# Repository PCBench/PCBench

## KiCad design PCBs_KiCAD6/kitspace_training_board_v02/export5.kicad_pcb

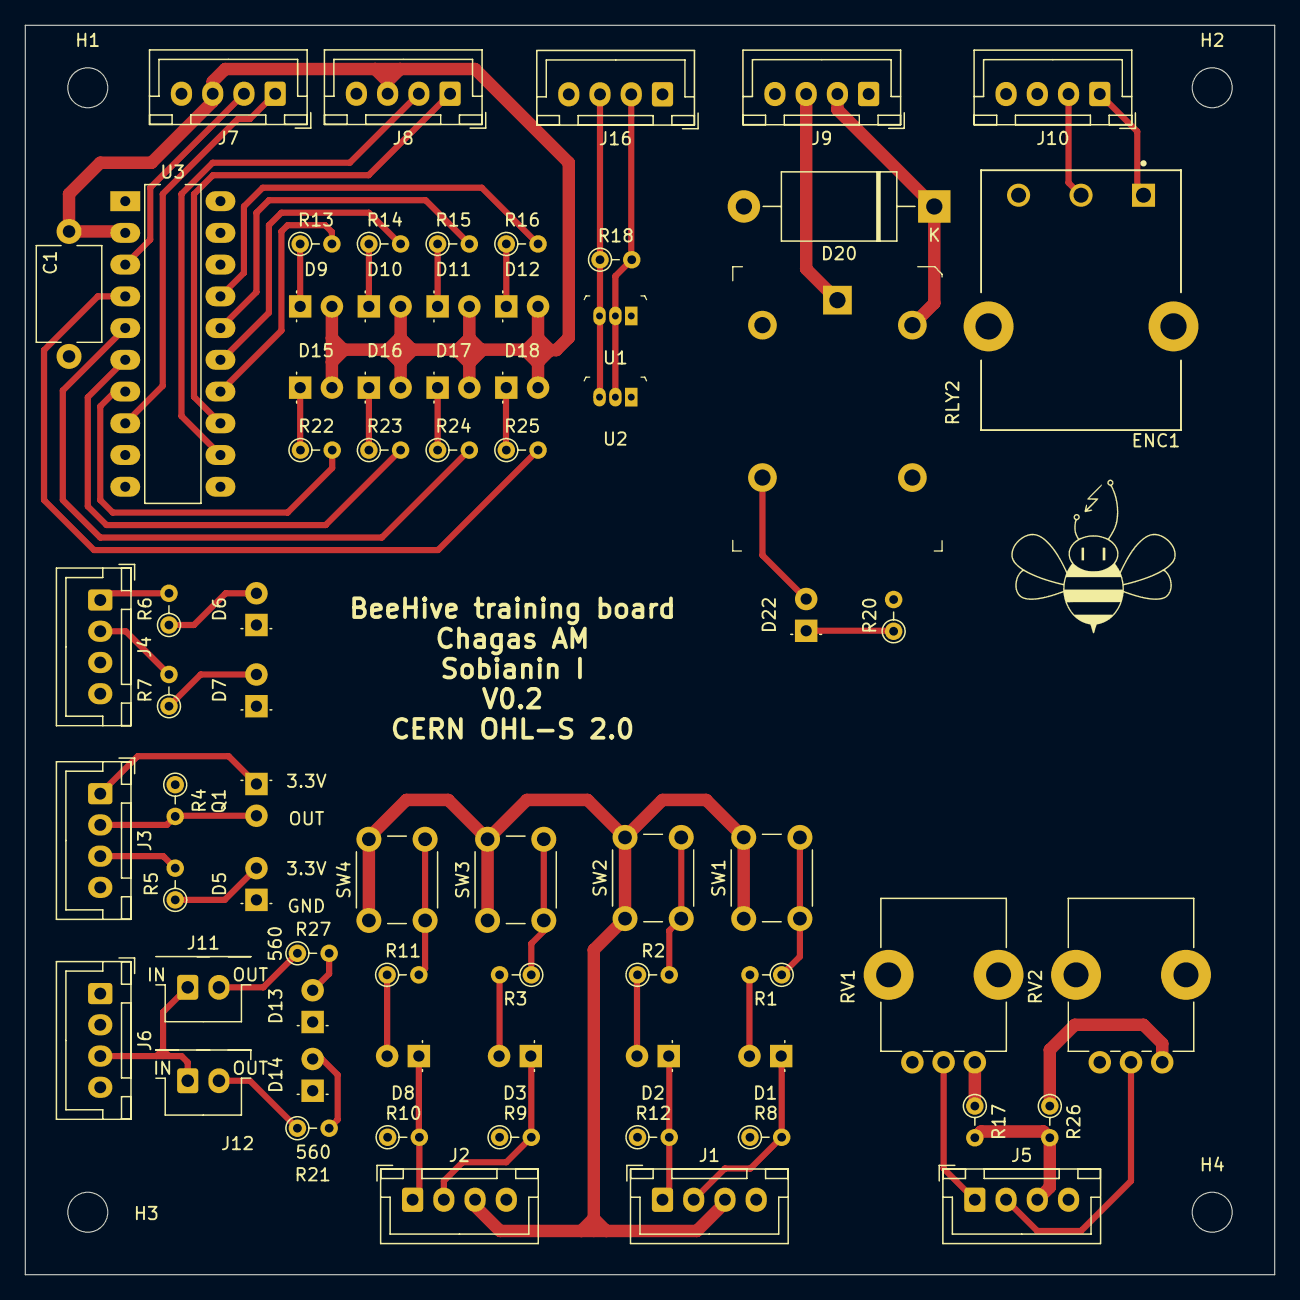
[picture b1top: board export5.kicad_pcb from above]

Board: 2 copper layers, 100.0 x 100.0 mm, 75 parts (0 on the bottom side), 61 nets.

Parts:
C1: 100nf; C_Disc_D7.5mm_W5.0mm_P10.00mm
D1, D2, D3, D6, D7, D8, D9, D10, D11, D12, D13, D14, D15, D16, D17, D18, D22: LED; LED_D3.0mm
D5: IR LED; LED_D3.0mm
D20: D_Schottky; D_DO-201AE_P15.24mm_Horizontal
ENC1: PEC16-4015F-N0024; Bourns_Inc.-PEC16-4015F-N0024-MFG
H1, H2, H3, H4: MountingHole; MountingHole_3.2mm_M3_DIN965
J1, J2, J3, J4, J5, J6, J7, J8, J9, J10, J16: Conn_01x04; JST_XH_B4B-XH-A_1x04_P2.50mm_Vertical
J11, J12: Conn_01x02; JST_XH_B2B-XH-A_1x02_P2.50mm_Vertical
Q1: Q_Photo_NPN; LED_D3.0mm
R1, R2, R3, R6, R7, R11: 220; R_Axial_DIN0204_L3.6mm_D1.6mm_P2.54mm_Vertical
R4: 10k; R_Axial_DIN0204_L3.6mm_D1.6mm_P2.54mm_Vertical
R5: 47; R_Axial_DIN0204_L3.6mm_D1.6mm_P2.54mm_Vertical
R8, R9, R10, R12: 1k; R_Axial_DIN0204_L3.6mm_D1.6mm_P2.54mm_Vertical
R13, R14, R15, R16, R20, R21, R22, R23, R24, R25, R27: 560; R_Axial_DIN0204_L3.6mm_D1.6mm_P2.54mm_Vertical
R17, R26: 5.6k; R_Axial_DIN0204_L3.6mm_D1.6mm_P2.54mm_Vertical
R18: 4.7k; R_Axial_DIN0204_L3.6mm_D1.6mm_P2.54mm_Vertical
RLY2: G5LE-14_DC5; Relay_THT_G5LE-14
RV1, RV2: 1k; Potentiometer_Alps_RK09K_Single_Vertical
SW1, SW2, SW3, SW4: SW_Push; SW_PUSH_6mm
U1, U2: DS18S20_; TO-92-3
U3: TPIC6595; DIP-20_W7.62mm_LongPads

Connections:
GND: C1.1, D5.1, D6.1, D7.1, D13.1, D14.1, D20.2, ENC1.C, J1.4, J2.4, J3.4, J4.4, J5.4, J6.4, J7.4, J8.4, J9.4, J10.4, J16.4, R4.1, R8.1, R9.1, R10.1, R12.1, R20.2, RLY2.2, RV1.3, RV2.3, U1.1, U2.1, U3.1, U3.9, U3.10, U3.11, U3.19, U3.20
unnamed: D1.1, J1.2, R8.2
unnamed: D1.2, R1.2
unnamed: D2.1, J1.1, R12.2
unnamed: D2.2, R2.1
unnamed: D3.1, J2.2, R9.2
unnamed: D3.2, R3.2
unnamed: D5.2, R5.1
unnamed: D6.2, R6.1
unnamed: D7.2, R7.1
unnamed: D8.1, J2.1, R10.2
unnamed: D8.2, R11.1
unnamed: D9.1, R13.1
unnamed: D10.1, R14.1
unnamed: D11.1, R15.1
unnamed: D12.1, R16.1
unnamed: D13.2, R27.2
unnamed: D14.2, R21.2
unnamed: D15.1, R22.1
unnamed: D16.1, R23.1
unnamed: D17.1, R24.1
unnamed: D18.1, R25.1
unnamed: D20.1, J9.2, RLY2.5
unnamed: D22.1, R20.1
unnamed: D22.2, RLY2.3
unnamed: ENC1.A, J10.1
unnamed: ENC1.B, J10.2
unnamed: J3.1, Q1.1
unnamed: J3.2, Q1.2, R4.2
unnamed: J3.3, R5.2
unnamed: J4.1, R6.2
unnamed: J4.2, R7.2
unnamed: J5.1, RV1.2
unnamed: J5.2, RV2.2
unnamed: J5.3, R17.2, R26.2
unnamed: J6.3, J11.1, J12.1
unnamed: J7.1, U3.8
unnamed: J7.2, U3.3
unnamed: J8.1, U3.13
unnamed: J8.2, U3.12
unnamed: J9.3, RLY2.1
unnamed: J16.2, R18.2, U1.2, U2.2
unnamed: R1.1, SW1.2
unnamed: R2.2, SW2.2
unnamed: R3.1, SW3.2
unnamed: R11.2, SW4.2
unnamed: R13.2, U3.14
unnamed: R14.2, U3.15
unnamed: R15.2, U3.16
unnamed: R16.2, U3.17
unnamed: R17.1, RV1.1
unnamed: J12.2, R21.1
unnamed: R22.2, U3.7
unnamed: R23.2, U3.6
unnamed: R24.2, U3.5
unnamed: R25.2, U3.4
unnamed: R26.1, RV2.1
unnamed: J11.2, R27.1
button_5v: J1.3, J2.3, SW1.1, SW2.1, SW3.1, SW4.1
reg_5V: C1.2, D9.2, D10.2, D11.2, D12.2, D15.2, D16.2, D17.2, D18.2, J7.3, J8.3, U3.2
temp_5V: J16.3, R18.1, U1.3, U2.3

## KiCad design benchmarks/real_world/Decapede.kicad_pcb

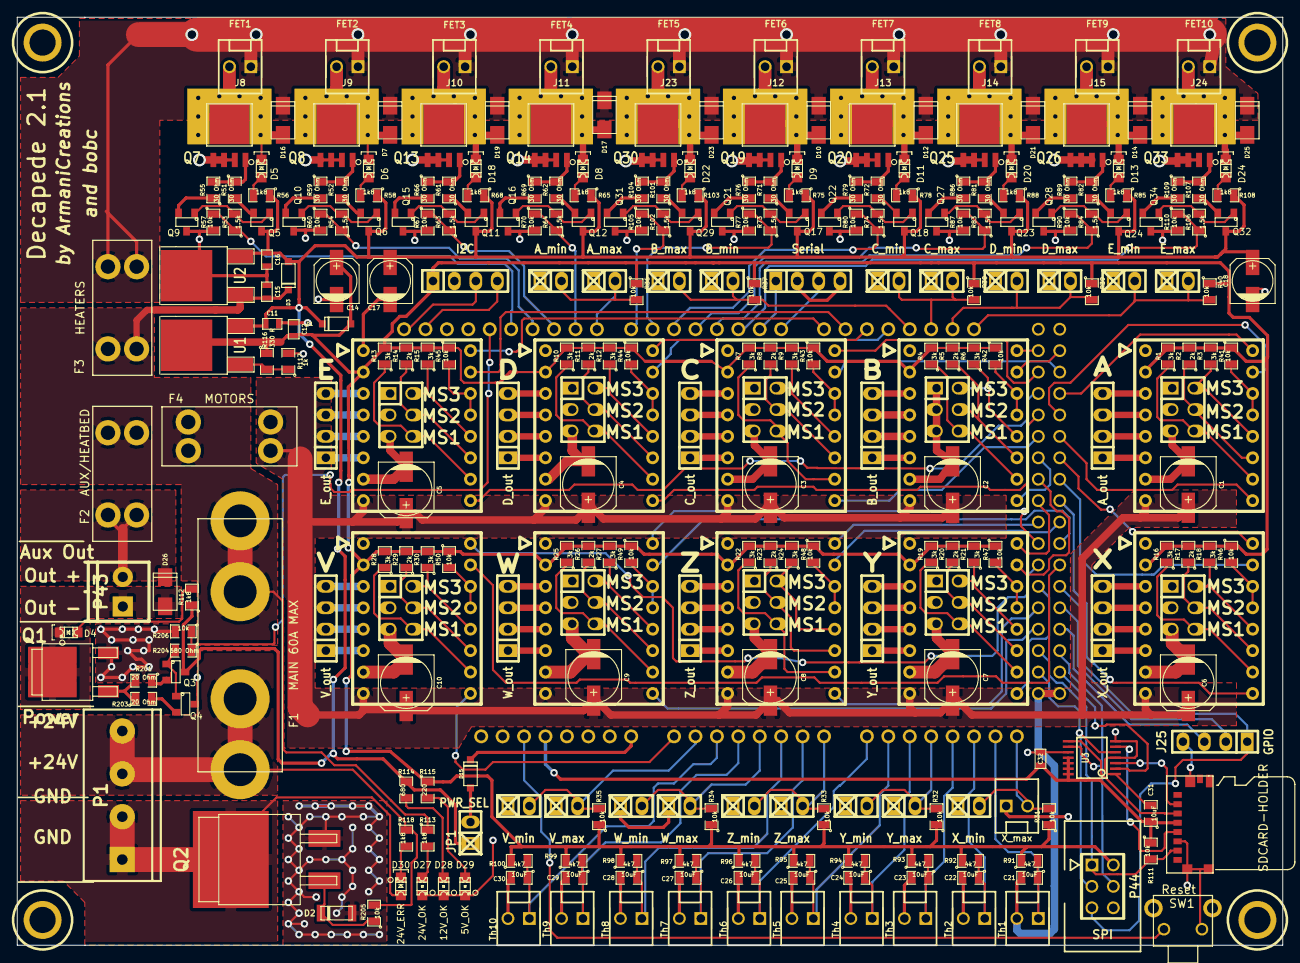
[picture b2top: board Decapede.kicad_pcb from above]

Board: 2 copper layers, 150.0 x 110.0 mm, 308 parts (0 on the bottom side), 241 nets.

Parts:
C1, C2, C3, C4, C5, C6, C7, C8, C9, C10: 100uF/35V; c_elec_6.3x7.7
C11, C15: 0.33uF; SM0603
C12, C16, C32: 0.1uF; SM0603
C14, C17, C18: 47uF; c_elec_5x5.3
C21, C22, C23, C24, C25, C26, C27, C28, C29, C30, C31: 10uF; SM0805
D1, D3, D15: Diode 1N4007; sod123
D2: BZV55-B15,115; sod80c
D4, D5, D6, D8, D9, D11, D13, D18, D20, D22, D24: LED; LED-0805_RED
D7, D10, D12, D14, D16, D17, D19, D21, D23, D25, D26: ES1D; do214ac
D27: 24V_OK; LED-0805_GREEN
D28: 12V_OK; LED-0805_GREEN
D29: 5V_OK; LED-0805_GREEN
D30: 24V_ERR; LED-0805_RED
F1: MAIN 60A MAX; FUSE_MAXI
F2: AUX/HEATBED; Keystone_3568
F3: HEATERS; Keystone_3568
F4: MOTORS; Keystone_3568
H1, H2, H3, H4: HOLE_RMC; HOLE_M3
J1: I2C; pin_strip_4
J8: FET1; CONN_KK_2.54_2W
J9: FET2; CONN_KK_2.54_2W
J10: FET3; CONN_KK_2.54_2W
J11: FET4; CONN_KK_2.54_2W
J12: FET6; CONN_KK_2.54_2W
J13: FET7; CONN_KK_2.54_2W
J14: FET8; CONN_KK_2.54_2W
J15: FET9; CONN_KK_2.54_2W
J16: Th1; CONN_KK_2.54_2W
J17: Th2; CONN_KK_2.54_2W
J18: Th3; CONN_KK_2.54_2W
J19: Th4; CONN_KK_2.54_2W
J20: Th5; CONN_KK_2.54_2W
J21: Th6; CONN_KK_2.54_2W
J22: Th7; CONN_KK_2.54_2W
J23: FET5; CONN_KK_2.54_2W
J24: FET10; CONN_KK_2.54_2W
J25: GPIO; pin_strip_4
J27: SDCARD-HOLDER; SD_MOLEX_47579-0001
J28: Th8; CONN_KK_2.54_2W
J29: Th9; CONN_KK_2.54_2W
J30: Th10; CONN_KK_2.54_2W
JP1: PWR_SEL; pin_strip_2
M1: PCB_GREEN_RMC
P1: Power; mors_4p
P2: MS_A; pin_strip_3x2
P3: A_out; pin_strip_4
P4: MS_B; pin_strip_3x2
P5: B_out; pin_strip_4
P6: C_out; pin_strip_4
P7: MS_C; pin_strip_3x2
P8: D_out; pin_strip_4
P9: MS_D; pin_strip_3x2
P10: E_out; pin_strip_4
P11: MS_E; pin_strip_3x2
P12: X_out; pin_strip_4
P13: MS_X; pin_strip_3x2
P14: Y_out; pin_strip_4
P15: MS_Y; pin_strip_3x2
P16: Z_out; pin_strip_4
P17: MS_Z; pin_strip_3x2
P18: W_out; pin_strip_4
P19: MS_W; pin_strip_3x2
P20: V_out; pin_strip_4
P21: MS_V; pin_strip_3x2
P22: X_min; pin_strip_2
P23: X_max; CONN_KK_2.54_2W
P24: Y_min; pin_strip_2
P25: Y_max; pin_strip_2
P26: Z_min; pin_strip_2
P27: Z_max; pin_strip_2
P28: W_min; pin_strip_2
P29: W_max; pin_strip_2
P30: V_min; pin_strip_2
P31: V_max; pin_strip_2
P32: A_min; pin_strip_2
P33: A_max; pin_strip_2
P34: B_min; pin_strip_2
P35: B_max; pin_strip_2
P36: C_min; pin_strip_2
P37: C_max; pin_strip_2
P38: D_min; pin_strip_2
P39: D_max; pin_strip_2
P40: E_min; pin_strip_2
P41: E_max; pin_strip_2
P42: Serial; pin_strip_4
P43: Aux Out; pt_1,5-2-3,5-h
P44: SPI; pin_array_3x2_RMC
Q1: BUK7226-75A,118; sot428-rmc
Q2: BUK964R8-60E,118; sot404
Q3, Q5, Q6, Q11, Q12, Q17, Q18, Q23, Q24, Q29, Q32: BC817-25,215; SOT23
Q4, Q9, Q10, Q15, Q16, Q21, Q22, Q27, Q28, Q31, Q34: BC807,215; SOT23
Q7, Q8, Q13, Q14, Q19, Q20, Q25, Q26, Q30, Q33: PSMN023-40YLCX; SOT669-PSMN023-ENH_RMC
R1, R3, R4, R6, R7, R9, R10, R12, R13, R15, R16, R18, R19, R21, R22, R24, R25, R27, R28, R30: 3k; SM0805
R2, R5, R8, R11, R14, R17, R20, R23, R26, R29: 2k; SM0805
R31, R32, R33, R34, R35, R36, R37, R38, R39, R40, R41, R42, R43, R44, R45, R46, R47, R48, R49, R50, R57, R60, R67, R70, R77, R80, R87, R90, R105, R110, R111, R205, R206: 10k; SM0805
R51, R52, R55, R59, R61, R62, R66, R69, R71, R72, R76, R79, R81, R82, R86, R89, R101, R104, R107, R109: 30 Ohm; SM0805
R53, R54, R63, R64, R73, R74, R83, R84, R102, R106: 1.5k; SM0805
R56, R58, R65, R68, R75, R78, R85, R88, R103, R108, R112, R113, R118: 1k8; SM0805
R91, R92, R93, R94, R95, R96, R97, R98, R99, R100: 4k7; SM0805
R114: 680; SM0805
R115: 220; SM0805
R116: 330 R; SM0805
R117: 1k; SM0805
R201, R203: 20 Ohm; SM0805
R204: 680 Ohm; SM0805
SHIELD1: ARDUINO_SHIELD; ARDUINO_MEGA_R3_NO_MOUNT_RMC
SW1: Reset; SW_EVQ-PF303M
StepStick_1: STEPSTICK_A; StepStick
StepStick_2: STEPSTICK_B; StepStick
StepStick_3: STEPSTICK_C; StepStick
StepStick_4: STEPSTICK_D; StepStick
StepStick_5: STEPSTICK_E; StepStick
StepStick_6: STEPSTICK_X; StepStick
StepStick_7: STEPSTICK_Y; StepStick
StepStick_8: STEPSTICK_Z; StepStick
StepStick_9: STEPSTICK_W; StepStick
StepStick_10: STEPSTICK_V; StepStick
U1: LM317MDT; DPAK2
U2: L78M12CDT-TR; DPAK2
U3: 74LCX125; TSSOP14

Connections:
+3.3V: C31.1, C32.1, J27.4, R111.1, SHIELD1.3V3, U3.11, U3.12, U3.13, U3.14
+24V: C15.1, D3.2, F1.1, F2.2, F3.2, F4.2, R113.1, U2.1
+V_GATE: C11.1, C16.1, C17.1, C18.1, D1.2, D3.1, JP1.1, Q3.3, Q5.3, Q6.3, Q11.3, Q12.3, Q17.3, Q18.3, Q23.3, Q24.3, Q29.3, Q32.3, R56.1, R58.1, R65.1, R68.1, R75.1, R78.1, R85.1, R88.1, R103.1, R108.1, R112.1, R114.1, U1.3, U2.3
+V_HEATBED: D26.2, F2.1, P43.2
+V_HEATERS: D7.2, D10.2, D12.2, D14.2, D16.2, D17.2, D19.2, D21.2, D23.2, D25.2, F3.1, J8.1, J9.1, J10.1, J11.1, J12.1, J13.1, J14.1, J15.1, J23.1, J24.1
+V_LOGIC: C12.1, C14.1, D1.1, J1.1, P44.2, R1.2, R2.2, R3.2, R4.2, R5.2, R6.2, R7.2, R8.2, R9.2, R10.2, R11.2, R12.2, R13.2, R14.2, R15.2, R16.2, R17.2, R18.2, R19.2, R20.2, R21.2, R22.2, R23.2, R24.2, R25.2, R26.2, R27.2, R28.2, R29.2, R30.2, R31.1, R32.1, R33.1, R34.1, R35.1, R36.1, R37.1, R38.1, R39.1, R40.1, R41.1, R42.1, R43.1, R44.1, R45.1, R46.1, R47.1, R48.1, R49.1, R50.1, R91.1, R92.1, R93.1, R94.1, R95.1, R96.1, R97.1, R98.1, R99.1, R100.1, R115.1, R116.1, StepStick_1.2, StepStick_2.2, StepStick_3.2, StepStick_4.2, StepStick_5.2, StepStick_6.2, StepStick_7.2, StepStick_8.2, StepStick_9.2, StepStick_10.2, U1.2
+V_MOTOR: C1.1, C2.1, C3.1, C4.1, C5.1, C6.1, C7.1, C8.1, C9.1, C10.1, F4.1, StepStick_1.8, StepStick_2.8, StepStick_3.8, StepStick_4.8, StepStick_5.8, StepStick_6.8, StepStick_7.8, StepStick_8.8, StepStick_9.8, StepStick_10.8
/FET Drivers/FET1_OUT: D5.2, D16.1, J8.2, Q7.5
/FET Drivers/FET2_OUT: D6.2, D7.1, J9.2, Q8.5
/FET Drivers/FET3_OUT: D18.2, D19.1, J10.2, Q13.5
/FET Drivers/FET_OUT4: D8.2, D17.1, J11.2, Q14.5
/FET PWM Drivers/FET_OUT_P1: D9.2, D10.1, J12.2, Q19.5
/FET PWM Drivers/FET_OUT_P2: D11.2, D12.1, J13.2, Q20.5
/FET PWM Drivers/FET_OUT_P3: D20.2, D21.1, J14.2, Q25.5
/FET PWM Drivers/FET_OUT_P4: D13.2, D14.1, J15.2, Q26.5
/More FET drivers/FET_OUT_5: D22.2, D23.1, J23.2, Q30.5
/More FET drivers/FET_OUT_P5: D24.2, D25.1, J24.2, Q33.5
/Power/24V_IN: F1.2, P1.3, P1.4, R118.1, R205.2
/Power/AUX_RTN: D4.2, D26.1, P43.1, Q1.2
/Power/GND_IN: D30.1, P1.1, P1.2, Q2.2
/Stepstick/MOT_1A_A: P3.3, StepStick_1.4
/Stepstick/MOT_1A_B: P5.3, StepStick_2.4
/Stepstick/MOT_1A_C: P6.3, StepStick_3.4
/Stepstick/MOT_1A_D: P8.3, StepStick_4.4
/Stepstick/MOT_1A_E: P10.3, StepStick_5.4
/Stepstick/MOT_1A_V: P20.3, StepStick_10.4
/Stepstick/MOT_1A_W: P18.3, StepStick_9.4
/Stepstick/MOT_1A_X: P12.3, StepStick_6.4
/Stepstick/MOT_1A_Y: P14.3, StepStick_7.4
/Stepstick/MOT_1A_Z: P16.3, StepStick_8.4
/Stepstick/MOT_1B_A: P3.4, StepStick_1.3
/Stepstick/MOT_1B_B: P5.4, StepStick_2.3
/Stepstick/MOT_1B_C: P6.4, StepStick_3.3
/Stepstick/MOT_1B_D: P8.4, StepStick_4.3
/Stepstick/MOT_1B_E: P10.4, StepStick_5.3
/Stepstick/MOT_1B_V: P20.4, StepStick_10.3
/Stepstick/MOT_1B_W: P18.4, StepStick_9.3
/Stepstick/MOT_1B_X: P12.4, StepStick_6.3
/Stepstick/MOT_1B_Y: P14.4, StepStick_7.3
/Stepstick/MOT_1B_Z: P16.4, StepStick_8.3
/Stepstick/MOT_2A_A: P3.2, StepStick_1.5
/Stepstick/MOT_2A_B: P5.2, StepStick_2.5
/Stepstick/MOT_2A_C: P6.2, StepStick_3.5
/Stepstick/MOT_2A_D: P8.2, StepStick_4.5
/Stepstick/MOT_2A_E: P10.2, StepStick_5.5
/Stepstick/MOT_2A_V: P20.2, StepStick_10.5
/Stepstick/MOT_2A_W: P18.2, StepStick_9.5
/Stepstick/MOT_2A_X: P12.2, StepStick_6.5
/Stepstick/MOT_2A_Y: P14.2, StepStick_7.5
/Stepstick/MOT_2A_Z: P16.2, StepStick_8.5
/Stepstick/MOT_2B_A: P3.1, StepStick_1.6
/Stepstick/MOT_2B_B: P5.1, StepStick_2.6
/Stepstick/MOT_2B_C: P6.1, StepStick_3.6
/Stepstick/MOT_2B_D: P8.1, StepStick_4.6
/Stepstick/MOT_2B_E: P10.1, StepStick_5.6
/Stepstick/MOT_2B_V: P20.1, StepStick_10.6
/Stepstick/MOT_2B_W: P18.1, StepStick_9.6
/Stepstick/MOT_2B_X: P12.1, StepStick_6.6
/Stepstick/MOT_2B_Y: P14.1, StepStick_7.6
/Stepstick/MOT_2B_Z: P16.1, StepStick_8.6
AGND: C21.2, C22.2, C23.2, C24.2, C25.2, C26.2, C27.2, C28.2, C29.2, C30.2, J16.2, J17.2, J18.2, J19.2, J20.2, J21.2, J22.2, J28.2, J29.2, J30.2, SHIELD1.GND4, SHIELD1.GND5
ARDUINO_VIN: D15.2, SHIELD1.V_IN
A_axis: P32.2, P33.2, R36.2, SHIELD1.8
Aux_output: R204.1, R206.1, SHIELD1.13
B_axis: P34.2, P35.2, R37.2, SHIELD1.18
C_axis: P36.2, P37.2, R38.2, SHIELD1.19
D_axis: P38.2, P39.2, R39.2, SHIELD1.20
E_axis: P40.2, P41.2, R40.2, SHIELD1.21
FET1: R53.1, R57.1, SHIELD1.12
FET1_PWM: R73.1, R77.1, SHIELD1.6
FET2: R54.1, R60.1, SHIELD1.11
FET2_PWM: R74.1, R80.1, SHIELD1.5
FET3: R63.1, R67.1, SHIELD1.10
FET3_PWM: R83.1, R87.1, SHIELD1.4
FET4: R64.1, R70.1, SHIELD1.9
FET4_PWM: R84.1, R90.1, SHIELD1.3
FET5: R102.1, R105.1, SHIELD1.7
FET5_PWM: R106.1, R110.1, SHIELD1.2
GND: C1.2, C2.2, C3.2, C4.2, C5.2, C6.2, C7.2, C8.2, C9.2, C10.2, C11.2, C12.2, C14.2, C15.2, C16.2, C17.2, C18.2, C31.2, C32.2, D2.1, D27.2, D28.2, D29.2, J1.2, J25.4, J27.6, J27.9, J27.10, J27.11, P2.1, P2.3, P2.5, P4.1, P4.3, P4.5, P7.1, P7.3, P7.5, P9.1, P9.3, P9.5, P11.1, P11.3, P11.5, P13.1, P13.3, P13.5, P15.1, P15.3, P15.5, P17.1, P17.3, P17.5, P19.1, P19.3, P19.5, P21.1, P21.3, P21.5, P22.1, P23.1, P24.1, P25.1, P26.1, P27.1, P28.1, P29.1, P30.1, P31.1, P32.1, P33.1, P34.1, P35.1, P36.1, P37.1, P38.1, P39.1, P40.1, P41.1, P42.2, P42.4, P44.6, Q1.3, Q2.3, Q4.3, Q7.1, Q8.1, Q9.3, Q10.3, Q13.1, Q14.1, Q15.3, Q16.3, Q19.1, Q20.1, Q21.3, Q22.3, Q25.1, Q26.1, Q27.3, Q28.3, Q30.1, Q31.3, Q33.1, Q34.3, R57.2, R60.2, R67.2, R70.2, R77.2, R80.2, R87.2, R90.2, R105.2, R110.2, R117.2, R206.2, SHIELD1.GND, SW1.2, StepStick_1.1, StepStick_1.7, StepStick_2.1, StepStick_2.7, StepStick_3.1, StepStick_3.7, StepStick_4.1, StepStick_4.7, StepStick_5.1, StepStick_5.7, StepStick_6.1, StepStick_6.7, StepStick_7.1, StepStick_7.7, StepStick_8.1, StepStick_8.7, StepStick_9.1, StepStick_9.7, StepStick_10.1, StepStick_10.7, U2.2, U3.1, U3.4, U3.7, U3.10
GPIO1: J25.1, P44.5, SHIELD1.45
GPIO2: J25.2, SHIELD1.47
GPIO3: J25.3, SHIELD1.49
MISO: J27.7, P44.1, R111.2, SHIELD1.50
MOSI: P44.4, SHIELD1.51, U3.9
MotorA_Enable: SHIELD1.31, StepStick_1.9
MotorA_dir: SHIELD1.27, StepStick_1.16
MotorA_step: SHIELD1.29, StepStick_1.15
MotorB_Enable: SHIELD1.32, StepStick_2.9
MotorB_dir: SHIELD1.22, StepStick_2.16
MotorB_step: SHIELD1.23, StepStick_2.15
MotorC_Enable: SHIELD1.30, StepStick_3.9
MotorC_dir: SHIELD1.24, StepStick_3.16
MotorC_step: SHIELD1.25, StepStick_3.15
MotorD_Enable: SHIELD1.28, StepStick_4.9
MotorD_dir: SHIELD1.16, StepStick_4.16
MotorD_step: SHIELD1.17, StepStick_4.15
MotorE_Enable: SHIELD1.26, StepStick_5.9
MotorE_dir: SHIELD1.14, StepStick_5.16
MotorE_step: SHIELD1.15, StepStick_5.15
MotorV_Enable: SHIELD1.AD0, StepStick_10.9
MotorV_dir: SHIELD1.42, StepStick_10.16
MotorV_step: SHIELD1.43, StepStick_10.15
MotorW_Enable: SHIELD1.48, StepStick_9.9
MotorW_dir: SHIELD1.40, StepStick_9.16
MotorW_step: SHIELD1.41, StepStick_9.15
MotorX_Enable: SHIELD1.37, StepStick_6.9
MotorX_dir: SHIELD1.33, StepStick_6.16
MotorX_step: SHIELD1.35, StepStick_6.15
MotorY_Enable: SHIELD1.44, StepStick_7.9
MotorY_dir: SHIELD1.36, StepStick_7.16
MotorY_step: SHIELD1.34, StepStick_7.15
MotorZ_Enable: SHIELD1.46, StepStick_8.9
MotorZ_dir: SHIELD1.38, StepStick_8.16
MotorZ_step: SHIELD1.39, StepStick_8.15
unnamed: D28.1, R114.2
unnamed: D29.1, R115.2
unnamed: D27.1, R113.2
unnamed: R116.2, R117.1, U1.1
unnamed: D4.1, R112.2
unnamed: D15.1, JP1.2
unnamed: Q1.1, R201.2, R203.1
unnamed: D30.2, R118.2
unnamed: Q4.2, R203.2
unnamed: Q3.2, R201.1
unnamed: Q3.1, Q4.1, R204.2
unnamed: D2.2, Q2.1, R205.1
unnamed: P15.4, R20.1, StepStick_7.11
unnamed: P15.2, R21.1, StepStick_7.12
unnamed: R47.2, StepStick_7.13, StepStick_7.14
unnamed: P15.6, R19.1, StepStick_7.10
unnamed: R45.2, StepStick_5.13, StepStick_5.14
unnamed: P11.6, R13.1, StepStick_5.10
unnamed: P11.2, R15.1, StepStick_5.12
unnamed: P11.4, R14.1, StepStick_5.11
unnamed: R46.2, StepStick_6.13, StepStick_6.14
unnamed: P13.2, R18.1, StepStick_6.12
unnamed: P13.4, R17.1, StepStick_6.11
unnamed: P13.6, R16.1, StepStick_6.10
unnamed: R50.2, StepStick_10.13, StepStick_10.14
unnamed: P21.6, R28.1, StepStick_10.10
unnamed: P21.4, R29.1, StepStick_10.11
unnamed: P21.2, R30.1, StepStick_10.12
unnamed: P17.4, R23.1, StepStick_8.11
unnamed: P17.6, R22.1, StepStick_8.10
unnamed: P17.2, R24.1, StepStick_8.12
unnamed: R48.2, StepStick_8.13, StepStick_8.14
unnamed: P19.2, R27.1, StepStick_9.12
unnamed: P19.4, R26.1, StepStick_9.11
unnamed: P19.6, R25.1, StepStick_9.10
unnamed: R49.2, StepStick_9.13, StepStick_9.14
unnamed: P4.4, R5.1, StepStick_2.11
unnamed: P4.2, R6.1, StepStick_2.12
unnamed: R42.2, StepStick_2.13, StepStick_2.14
unnamed: P4.6, R4.1, StepStick_2.10
unnamed: P2.4, R2.1, StepStick_1.11
unnamed: P2.2, R3.1, StepStick_1.12
unnamed: R41.2, StepStick_1.13, StepStick_1.14
unnamed: P2.6, R1.1, StepStick_1.10
unnamed: R44.2, StepStick_4.13, StepStick_4.14
unnamed: P9.2, R12.1, StepStick_4.12
unnamed: P9.4, R11.1, StepStick_4.11
unnamed: P9.6, R10.1, StepStick_4.10
unnamed: P7.6, R7.1, StepStick_3.10
unnamed: R43.2, StepStick_3.13, StepStick_3.14
unnamed: P7.4, R8.1, StepStick_3.11
unnamed: P7.2, R9.1, StepStick_3.12
unnamed: Q8.4, R52.2, R59.1
unnamed: D8.1, R65.2
unnamed: Q11.2, R61.1
unnamed: Q13.4, R61.2, R66.1
unnamed: Q15.2, R66.2
unnamed: Q11.1, Q15.1, R63.2
unnamed: Q6.1, Q10.1, R54.2
unnamed: Q6.2, R52.1
unnamed: Q10.2, R59.2
unnamed: Q7.4, R51.1, R55.2
unnamed: Q9.2, R55.1
unnamed: Q5.2, R51.2
unnamed: D6.1, R58.2
unnamed: D18.1, R68.2
unnamed: Q14.4, R62.2, R69.1
unnamed: Q5.1, Q9.1, R53.2
unnamed: D5.1, R56.2
unnamed: Q12.2, R62.1
unnamed: Q16.2, R69.2
unnamed: Q12.1, Q16.1, R64.2
unnamed: Q28.2, R89.2
unnamed: Q24.1, Q28.1, R84.2
unnamed: Q26.4, R82.2, R89.1
unnamed: Q24.2, R82.1
unnamed: D9.1, R75.2
unnamed: Q18.1, Q22.1, R74.2
unnamed: Q22.2, R79.2
unnamed: Q18.2, R72.1
unnamed: Q23.2, R81.1
unnamed: Q25.4, R81.2, R86.1
unnamed: Q27.2, R86.2
unnamed: Q23.1, Q27.1, R83.2
unnamed: Q20.4, R72.2, R79.1
unnamed: D11.1, R78.2
unnamed: Q19.4, R71.2, R76.1
unnamed: D20.1, R88.2
unnamed: D13.1, R85.2
unnamed: Q21.2, R76.2
unnamed: Q17.2, R71.1
unnamed: Q17.1, Q21.1, R73.2
unnamed: D24.1, R108.2
unnamed: Q32.1, Q34.1, R106.2
unnamed: Q33.4, R107.2, R109.1
unnamed: Q30.4, R101.2, R104.1
unnamed: D22.1, R103.2
unnamed: Q29.2, R101.1
unnamed: Q31.2, R104.2
unnamed: Q29.1, Q31.1, R102.2
unnamed: Q34.2, R109.2
unnamed: Q32.2, R107.1
unnamed: J27.3, U3.8
unnamed: J27.5, U3.6
unnamed: J27.2, U3.3
Reset: SHIELD1.RST, SW1.1
Rx0: P42.3, SHIELD1.0
SCK: P44.3, SHIELD1.52, U3.5
SCL1: J1.3, SHIELD1.SCL1
SDA1: J1.4, SHIELD1.SDA1
SS: SHIELD1.53, U3.2
TH1: C21.1, J16.1, R91.2, SHIELD1.AD14
TH2: C22.1, J17.1, R92.2, SHIELD1.AD13
TH3: C23.1, J18.1, R93.2, SHIELD1.AD12
TH4: C24.1, J19.1, R94.2, SHIELD1.AD10
TH5: C25.1, J20.1, R95.2, SHIELD1.AD9
TH6: C26.1, J21.1, R96.2, SHIELD1.AD8
TH7: C27.1, J22.1, R97.2, SHIELD1.AD6
TH8: C28.1, J28.1, R98.2, SHIELD1.AD5
TH9: C29.1, J29.1, R99.2, SHIELD1.AD3
TH10: C30.1, J30.1, R100.2, SHIELD1.AD2
Tx0: P42.1, SHIELD1.1
V_axis: P30.2, P31.2, R35.2, SHIELD1.AD1
W_axis: P28.2, P29.2, R34.2, SHIELD1.AD4
X_axis: P22.2, P23.2, R31.2, SHIELD1.AD15
Y_axis: P24.2, P25.2, R32.2, SHIELD1.AD11
Z_axis: P26.2, P27.2, R33.2, SHIELD1.AD7

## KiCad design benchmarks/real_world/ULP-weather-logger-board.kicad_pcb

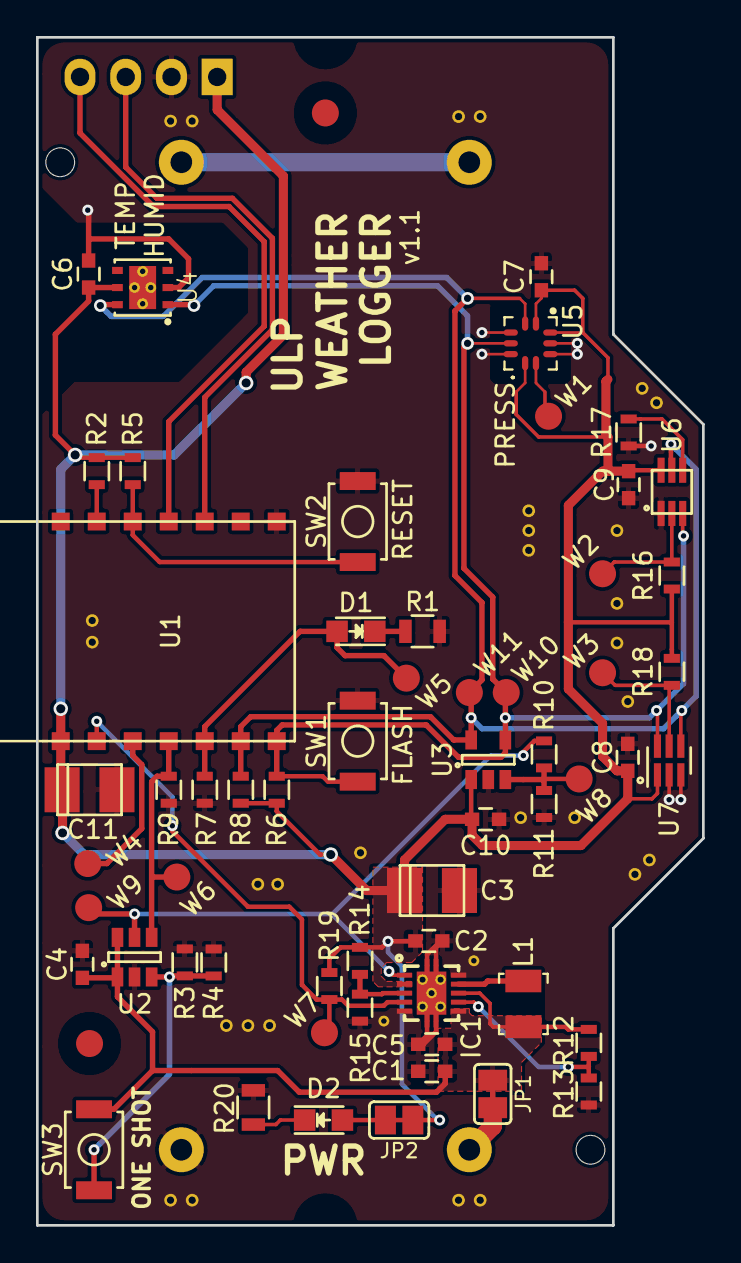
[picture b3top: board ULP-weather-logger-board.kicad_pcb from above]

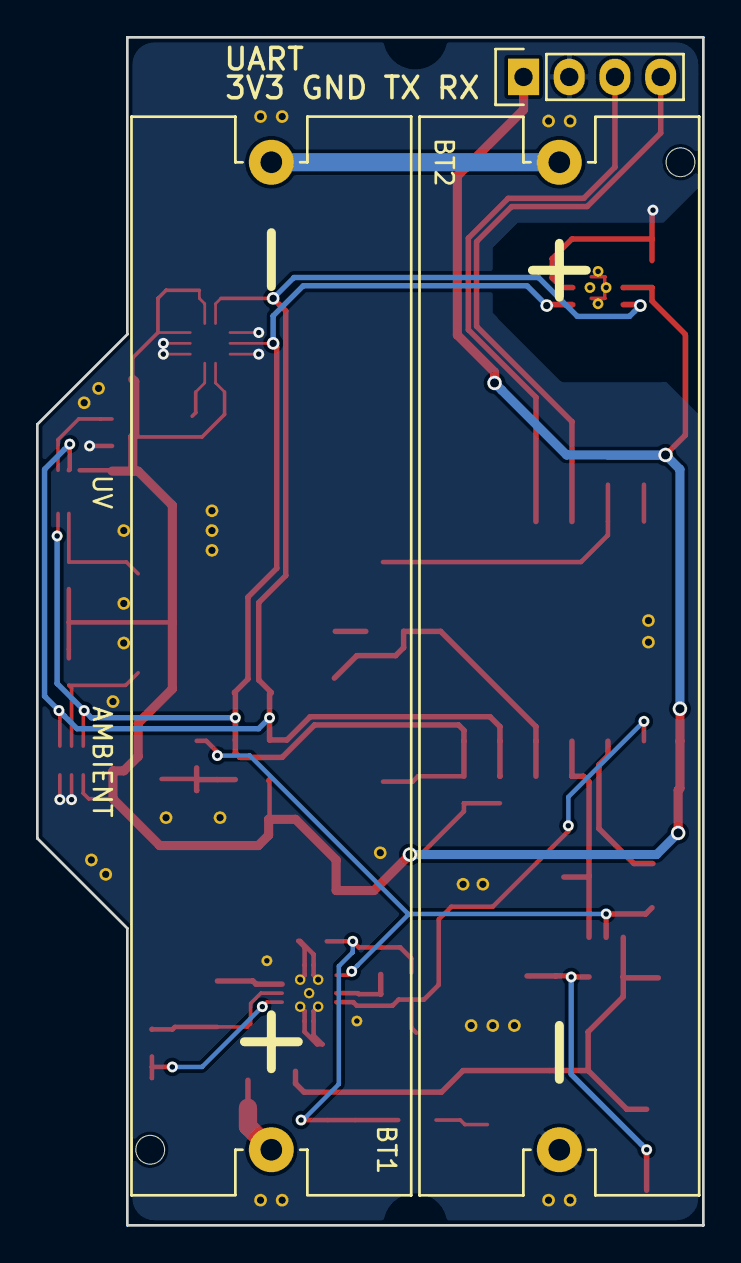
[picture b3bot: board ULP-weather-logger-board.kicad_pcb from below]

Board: 2 copper layers, 37.0 x 66.0 mm, 63 parts (3 on the bottom side), 26 nets.

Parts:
BT1, BT2: 1015; Keystone_1015_Holder_Battery_AA
C1: 10uF; C_0603
C2: 2.2uF; C_0603
C3: 100uF; TantalC_SizeB_EIA-3528_Reflow
C4, C5, C6, C7, C8, C9, C10: 0.1uF; C_0603
C11: DNP; TantalC_SizeB_EIA-3528_Reflow
D1, D2: LTST-C170KRKT; LED_0805
FID1, FID2: FIDUCIAL; Fiducial
IC1: TPS61025; TI_DRC_S-PVSON-N10
JP1, JP2: JUMPER; SJ_OPEN
L1: 6.8uH; Inductor_1210
P1: CONN_01X04; Pin_Header_Straight_1x04
R1, R20: 1k; R_0805
R2, R13, R14: 0R; R_0603
R3: 140k; R_0603
R4: 174k; R_0603
R5, R6, R7, R8, R9, R16, R18: 10k; R_0603
R10: 1k; R_0603
R11: 390k; R_0603
R12, R15: DNP; R_0603
R17: 270k; R_0603
R19: 1M; R_0603
SW1, SW2, SW3: PTS820 J15M SMTR LFS; Tact_Switch_Top_PTS820
U1: ESP8266-ESP-03
U2: TPL5111; SOT-23-6
U3: MCP3021; SOT-23-5
U4: HDC1080; WSON-6-PAD
U5: LPS25HB; ST_LPS25HB
U6: VEML6070; OPLGA6
U7: TSL2561; WDFN-6_2x2mm_Pitch0.65mm
W1: PRES_INT; Measurement_Point_Round-SMD-Pad_Small
W2: UV_INT; Measurement_Point_Round-SMD-Pad_Small
W3: AMB_INT; Measurement_Point_Round-SMD-Pad_Small
W4: GPIO_12; Measurement_Point_Round-SMD-Pad_Small
W5: L; Measurement_Point_Round-SMD-Pad_Small
W6: DONE; Measurement_Point_Round-SMD-Pad_Small
W7: LOWBATT; Measurement_Point_Round-SMD-Pad_Small
W8: BATT_VOUT; Measurement_Point_Round-SMD-Pad_Small
W9: DRVn; Measurement_Point_Round-SMD-Pad_Small
W10: SDA; Measurement_Point_Round-SMD-Pad_Small
W11: SCL; Measurement_Point_Round-SMD-Pad_Small

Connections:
+3V3: C2.1, C3.1, C6.1, C7.1, C8.1, C9.1, C10.1, C11.1, D2.2, IC1.2, JP2.1, JP2.2, P1.1, R2.1, R5.1, R6.1, R8.1, R14.1, R16.1, R18.1, R19.1, U1.8, U3.1, U4.5, U5.1, U5.6, U5.10, U6.6, U7.1
+BATT: BT1.1, C1.1, C4.1, C5.1, IC1.6, IC1.8, JP1.1, JP1.2, L1.1, R12.1, SW3.1, U2.1, U2.6
/BATT_VOUT: R10.2, R11.1, U3.3, W8.1
/DONE: R9.1, U1.11, U2.4, W6.1
/DRVn: IC1.1, R10.1, U2.5, W9.1
/FB: IC1.3, R14.2, R15.1
/GPIO_12: U1.10, W4.1
/L: D1.2, R7.1, U1.12, W5.1
/LBI: IC1.7, R12.2, R13.1
/LOWBATT: IC1.4, R19.2, U1.9, W7.1
/M_DRV: R3.1, R4.1, SW3.2, U2.3
/RX: P1.4, U1.4
/SCL: R8.2, U1.13, U3.5, U4.6, U5.2, U6.5, U7.4, W11.1
/SDA: R6.2, SW1.1, U1.14, U3.4, U4.1, U5.4, U6.3, U7.6, W10.1
/TX: P1.3, U1.3
GND: BT2.2, C1.2, C2.2, C3.2, C4.2, C5.2, C6.2, C7.2, C8.2, C9.2, C10.2, C11.2, IC1.0, IC1.5, IC1.10, P1.2, R1.2, R3.2, R4.2, R7.2, R9.2, R11.2, R13.2, R15.2, R17.1, R20.2, SW1.2, SW2.2, U1.1, U2.2, U3.2, U4.2, U5.3, U5.5, U5.8, U5.9, U6.1, U7.2, U7.3
unnamed: BT1.2, BT2.1
unnamed: D1.1, R1.1
unnamed: D2.1, R20.1
unnamed: IC1.9, L1.2
unnamed: R2.2, U1.6
unnamed: R5.2, SW2.1, U1.5
unnamed: R16.2, U6.2, W2.1
unnamed: R17.2, U6.4
unnamed: R18.2, U7.5, W3.1
unnamed: U5.7, W1.1

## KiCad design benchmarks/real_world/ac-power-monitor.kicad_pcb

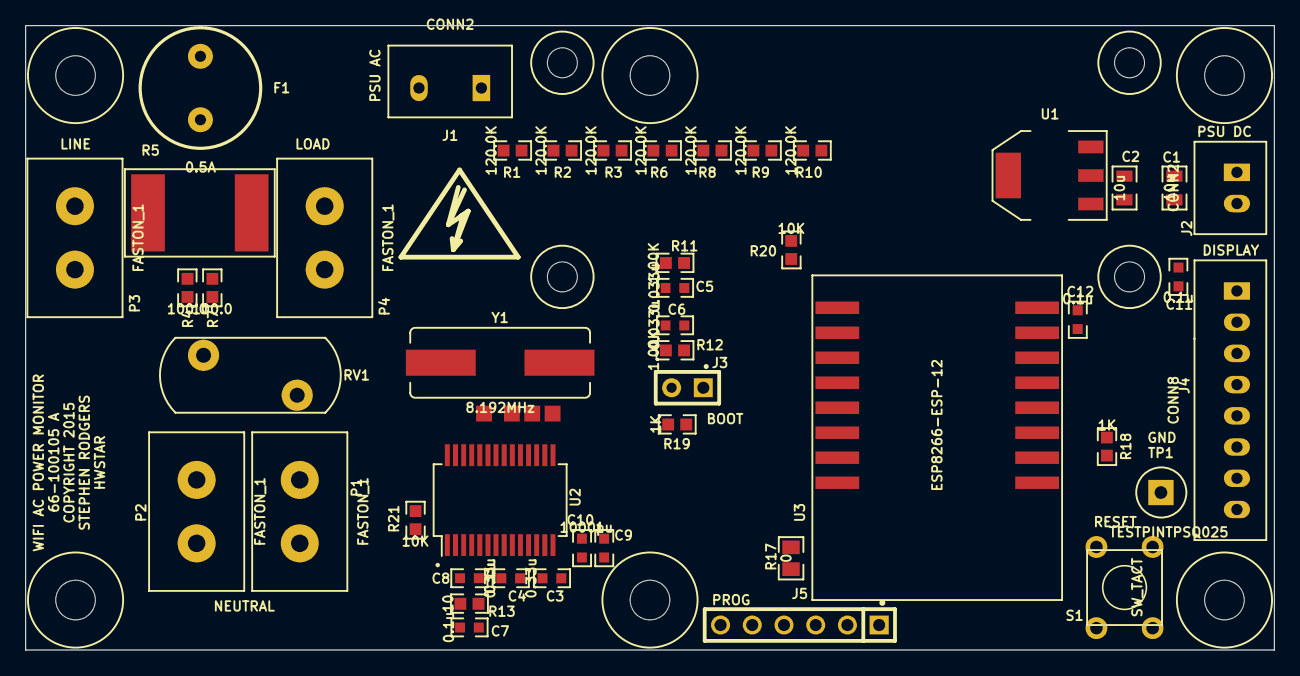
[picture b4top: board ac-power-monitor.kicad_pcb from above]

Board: 2 copper layers, 100.0 x 50.0 mm, 62 parts (0 on the bottom side), 35 nets, no tracks yet.

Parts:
C1, C2: 10u; CC0805
C3, C4: 0.33u; CC0603
C5, C6: 0.033u; CC0603
C7, C8, C11, C12: 0.1u; CC0603
C9: 1u; CC0603
C10: 1000p; CC0603
F1: 0.5A; BELFUSE_MRT
J1: CONN2; JST_B3B_SPECIAL
J2: CONN2; JST_B2B_XH_A
J3: CONN2; BERG2
J4: CONN8; JST_B8B_XH_A
J5: CONN6; BERG6
MTG-HOLE-125-RING-300, MTG-HOLE-125-RING-300#2, MTG-HOLE-125-RING-300#3, MTG-HOLE-125-RING-300#4, MTG-HOLE-125-RING-300#5, MTG-HOLE-125-RING-300#6: VAL**; MTG-HOLE-125-RING-300
MTG-HOLE-M2-RING-5MM, MTG-HOLE-M2-RING-5MM#2, MTG-HOLE-M2-RING-5MM#3, MTG-HOLE-M2-RING-5MM#4: VAL**; MTG-HOLE-M2-RING-5MM
P1, P2, P3, P4: FASTON_1; KEYSTONE_1287-ST
R1, R2, R3, R6, R8, R9, R10: 120.0K; RC0603
R4, R7: 100.0; RC0603
R5: 0.001; WSL3921
R11, R12: 1.00K; RC0603
R13: 10; RC0603
R17: 0; RC0805
R18, R19: 1K; RC0603
R20, R21: 10K; RC0603
RV1: MOV-10D431; VARISTOR-10D
S1: SW_TACT; SW_TACT_6MM
Sym: Symbol_HighVoltage_Type2_SilkTop_VerySmall
TP1: TESTPINTPSQ025; TESTPIN
TP2, TP3, TP4, TP5: TESTPINTPSQ025; TESTPAD
U1: AZ1117CH-3.3TRG1; SOT-223-SAR
U2: 90E24PYGI; SSOP28-SAR
U3: ESP8266-ESP-12; ESP8266-ESP12
Y1: 8.192MHz; HC49US-SAR

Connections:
+3.3V: C2.1, C7.1, C11.1, C12.1, J4.1, R13.1, R17.1, R18.1, R19.1, R20.1, R21.1, U1.2, U1.4, U2.3, U2.28, U3.3, U3.8
/Power/+5V: C1.1, J2.1, U1.3
/Power/HOT: F1.2, J1.2
/Power/LOAD: P4.1, P4.2, R5.2, R7.2
/Power/NEUTRAL: J1.1, P1.1, P1.2, P2.1, P2.2, R1.1, RV1.1
/WIFI/GPIO16: J4.7, U3.4
/WIFI/SPWR: J5.3, R17.2
GND: C1.2, C2.2, C3.2, C4.1, C5.2, C6.2, C7.2, C8.2, C9.2, C10.2, C11.2, C12.2, F1.1, J2.2, J3.2, J4.8, J5.1, P3.1, P3.2, R4.2, R5.1, R11.2, R12.2, RV1.2, S1.1, S1.2, TP1.1, U1.1, U2.1, U2.2, U2.6, U2.7, U2.8, U2.14, U2.24, U3.2, U3.9, U3.10
ISAMPLEN: C3.1, R4.1, U2.11
ISAMPLEP: C4.2, R7.1, U2.10
unnamed: C8.1, R13.2, U2.5
unnamed: C9.1, C10.1, U2.13
unnamed: J3.1, R19.2, U3.12
unnamed: J5.4, U3.15
unnamed: J5.5, U3.16
unnamed: R1.2, R2.1
unnamed: R2.2, R3.1
unnamed: R3.2, R6.1
unnamed: R6.2, R8.1
unnamed: R8.2, R9.1
unnamed: R9.2, R10.1
unnamed: R18.2, S1.3, S1.4, U3.1
unnamed: R20.2, U3.11
unnamed: R21.2, U2.4
unnamed: TP2.1, U2.18
unnamed: TP3.1, U2.19
unnamed: TP4.1, U2.21
unnamed: TP5.1, U2.17
unnamed: U2.22, Y1.2
unnamed: U2.23, Y1.1
SCLK: J4.4, U2.25, U3.6
SDI: J4.6, U2.27, U3.5
SDO: J4.5, U2.26, U3.7
VSAMPLEN: C6.1, R12.1, U2.15
VSAMPLEP: C5.1, R10.2, R11.1, U2.16

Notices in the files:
PCBs_KiCAD6/kitspace_training_board_v02/export5.kicad_pcb:
CERN OHL-S 2.0
benchmarks/real_world/ac-power-monitor.kicad_pcb:
COPYRIGHT 2015
benchmarks/real_world/cpu-board.kicad_pcb:
©2016 Rich Wareham
CC BY-NC-SA 4.0
